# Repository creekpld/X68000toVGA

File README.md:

# This is not the Repo you are looking for! :alien:

New development is taking place in [gitlab.com/pdylong/X68000toVGA](https://gitlab.com/pdylong/X68000toVGA) :ok_hand:.

# X68000toVGA

An RGB to VGA Monitor Adapter for the Sharp X68000.

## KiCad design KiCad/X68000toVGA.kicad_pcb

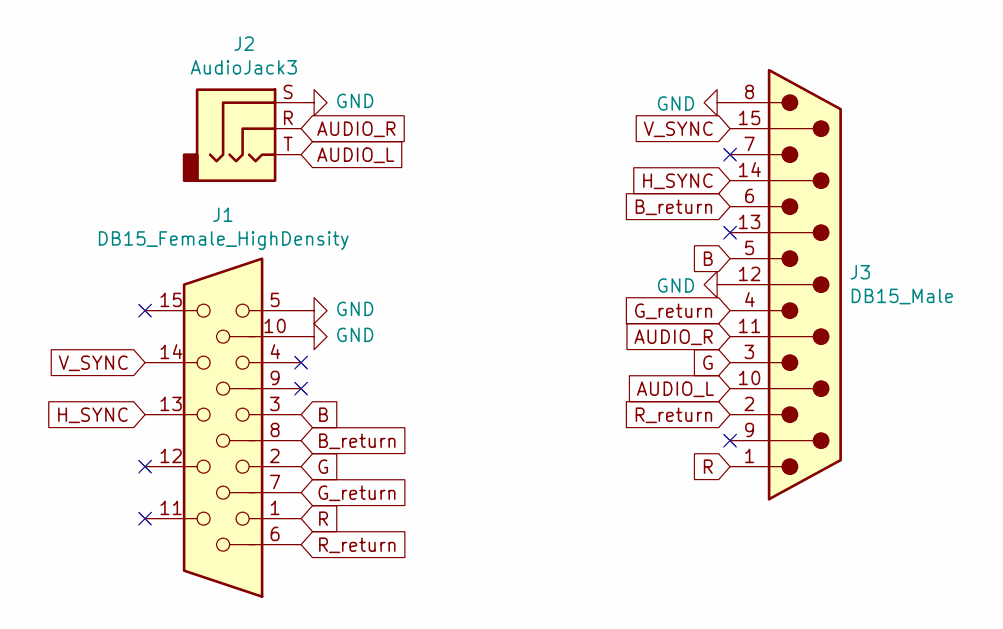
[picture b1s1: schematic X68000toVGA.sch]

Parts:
J1: DB15_Female_HighDensity; DSUB-15-HD_Female_Horizontal_P2.29x2.54mm_EdgePinOffset9.40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
J2: AudioJack3; ASJ-125-3
J3: DB15_Male; DSUB-15_Male_Horizontal_P2.77x2.54mm_EdgePinOffset9.40mm

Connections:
AUDIO_L: J2.T, J3.10
AUDIO_R: J2.R, J3.11 (P111)
B: J1.3, J3.5
B_return: J1.8, J3.6
G: J1.2, J3.3
GND: J1.5, J1.10, J2.S, J3.8, J3.12
G_return: J1.7, J3.4
H_SYNC: J1.13, J3.14
R: J1.1, J3.1
R_return: J1.6, J3.2
V_SYNC: J1.14, J3.15

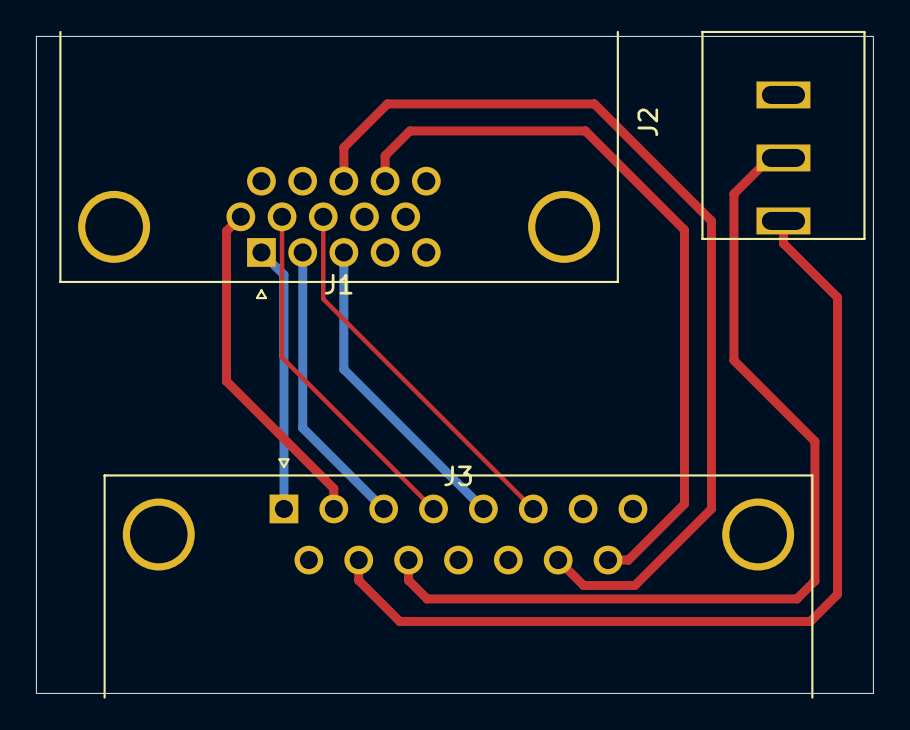
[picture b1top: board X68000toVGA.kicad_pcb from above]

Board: 2 copper layers, 46.5 x 36.5 mm, 3 parts (0 on the bottom side), 11 nets.

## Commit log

2019-05-28 :tada: first commit
2019-05-28 :construction: Work in progress
2020-07-21 Update README.md
    moving out
